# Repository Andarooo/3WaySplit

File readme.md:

# 3 Way Split

### An open source split keyboard. (yeah we really needed more of those (¬_¬) )

## Layout

As you might have guessed this keyboard is split into 3 parts. A left, right and numpad.
Left and right is split in the middle but follows a standard layout with the right side squished in and a couple extra macros for use on the left side.
Numpad has a couple extra macro keys as well if you want to use them.

## Firmware

Keyboard was made with intention to utilise [ZMK](https://zmk.dev/)
I have made a [matching ZMK repo](https://github.com/Andarooo/zmk-3waysplit) with config setup to take the expected layout with the assumption of a nice!nano or equivalent dev board has been used.

## Start Here

Let's say you want to take my slop of gerbers and STLs and make a functional keyboard what are we going to need?
 - Time & money
 - A 3D printer or a 3d printer service
 - A soldering iron
 - Time & money
 - Access to a PCB printing service like PCBWay or JLCPCB
 - A bunch of random crap most likely off Amazon (boo) or Ali-Express (not a boo but it's still not great)
 - Time & money

 If you have enough time and attention span that you're still reading then you might be in a hyperfocus spiral; maybe go get some more coffee. But also keep reading in order and you should have a decent idea on how to get this keeb up and running. I'll try to structure everything in the order that you would expect to do it in. Anyway, without further ado let's throw ourselves into:

 ## Parts

 So here's a list of all the random bits to get off your horrifying conglomerate market of choice:
 - SOD-123 diodes (107)
    - I went for 1n4148 but any that'll fit the sod-123 form and work with keebs will do.
 - Hotswap sockets (107)
    - These PCBs were made with the intended use of kailh hotswap sockets, any that fit will work so don't get too precious about it
 - Developer boards (3). 
    - The PCBs are made with the nice!nano in mind, you could modify the PCB files and regenerate gerbers and change that but if you're cabable of that why are you looking at my crappy design?
    - You could also use any of the knock of nice!nanos which are significantly cheaper (sorry Nick Winans); especially if you live outside the US. (googling pro micro or nice!nano will probably get you somewhere) 
        - The companies that make these are kinda trash because they're exploiting someone else's R&D. I you can buy the real deal pls do, but also business is business y'know.
    - You'll need one per part of the keeb so go ahead and buy 3.
 - M3 screw hot inserts.
    - You use a soldering iron to push these into a slot which adds a threaded insert so you can screw stuff together.
    - These are relatively cheap and you can buy the special soldering iron tips for pushing them in but you don't actually NEED them most of the time.
 - M3 screws.
    - What did you think the inserts were for?
    - You'll likely need a few sizes between 4mm to 20mm so I'd recommend just buying one of those assorted packs.
    - I chose to use allen/hex screws but any will do as long as the heads fit in the hole provided.
 - Keyswitches
    - It is a custom keeb, so I'd assume you knew about this one if you're reading this.
    - There's honestly too many options for me to go into here so I guess just google it or watch some weird cringy keebfluencer.
 - Keycaps
    - See above.
    - I did mess up and chose to have a 2.5u spacebar without realising they're actually pretty uncommon so you can eiter just use a 2.25u with a gap or go track one down. Most sets will have the 3u spacebar that I designed the right side for
 - Key stabilisers
    - These are for the longer keys.
    - All the stab slots are meant for the regular 2u stabs so don't get a spacebar stab; it won't get used. (I think there's 7?)
 - USB C cables to flash firmware and charge etc.

## PCB Printing

So this bit is actually way easier than it sounds, but you jump on the website of the pcb printer of our choice and upload the gerbers which are in the [gerber directory](https://github.com/Andarooo/3WaySplit/tree/main/PCB/Gerbers). It'll take a little while and for the most part just choose the standard settings. We only need the regular 2 layer PCB and also change the mask colour to whatever you'd like to see (I got purple).

## PCB Assembly

This keeb is actually pretty easy to assemble because I couldn't figure out how to get LEDs or even the caps/num/scroll locks lights working.

The keeb has 107 keys in total, does that mean you'll be soldering 107 parts? No of course not, you'll be soldering about 215. The parts that need to be soldered are SMD (Surface Mount Device) which are finicky as fuck to attach to a board if you don't know what the hell you're doing.

If you don't have any soldering experience you'll first want:
 - A soldering iron.
    - I recommend a cheap modern temperature controlled one like a pinecil or ts101 you'll need a fast charging brick that pumps out like 65W and a decent USB C cable too to power it. (Yes different cables will deliver different amounts of power)
 - Solder
    - I'd recommend leaded flux core as it's much easier to melt and work with, just don't lick it I guess.
 - Tip Tinner
    - It's like a powder which keeps your tip tinned (metal and shiny).
 - Flux resin/flux pen
    - For when the solder just doesn't wanna stick.
 - Wet sponge/paper towel
    - Gotta keep that tip clean.
 - A decent video on how to solder.

Soldering SMD parts can be annoying but in general it comes down to 3 steps:
1. Melt some solder onto 1 (not both) pad.
2. Put the part on and re-melt the solder to attach the part.
3. Add solder to the other pad to connect up the other side of the part.

It's much easier to do the sockets than the diodes because I'm an idiot and thought it'd be fun to choose the smaller SMD form factor.

***REMEMBER THAT DIODES HAVE A DIRECTION***

Don't solder them around the wrong way or the switch will not work. There's a thin line on one side which shows the cathode (-). This needs to go away from the the socket so make sure the side that you're soldering to the trace that goes straight to the socket doesn't have the line.

Similarly don't put the sockets on upside down, It'll be really obvious because you'll cover the hole that the middle of the switch usually goes in.

If you mess anything up then watch some videos on desoldering and buy some solder wick or a sucker I guess.

For the microcontroller board, there is some assumptions that I've made with regards to how it's mounted in my case design. If you don't want to mount it the same way I have planned then go and modify the case STLs. It's meant to be mounted with the standoffs on the underside of the case. The bottom of the dev board should be exposed. Just make sure the pins on the dev board match the keeb PCB and you should be sweet. Measure twice cut once. The USB C port should be exposed to the hole in the case if everything has been done right.

## Printing the case

This bit should be pretty straightforward if you've done some 3d printing before. 

There are 3 sets of parts; the plates, the enclosures and the feet. I would recommend printing the plates first to get an idea of how well your printer will handle it and if it will fit the build. The right side is the largest so if you can print the right enclosure you'll be g.

The case STLs are made up of a top and bottom piece, I'll leave that to you to work out on the slicer. They attach together later using the m3 screws and inserts.

I've never used a 3D printing service before so If you want to go that route I wish you luck but I can't provide advice.

## Adding the heated inserts

This part is actually pretty fun and satisfying. So as I alluded to earlier you can buy these special soldering iron tips that fit into the top of the m3 inserts. You don't need it and it doesn't make much difference TBH but It'll probably save you from accidentally poking the back of the hole with the tip of your iron.

There's not a whole lot to this really. make sure the insert is the right way around with the thinner bit going in first then push it in with the tip of your soldering iron giving light even pressure until it's fully seated. Preferably it should be flush with the surface, but if it goes a bit deep you just might need a slightly longer screw so nothing that bad. Try to keep it going in straight if you can.

Each top part of the enclosure has slots where the inserts are meant to go to support screws from the bottom.
Each bottom part has slots for where the feet will attach. ***Do not put the inserts in the screw holes which go all the way through**

## Firmware + Test

You should probably flash the firmware before you assemble as you'll need access to the controller boards to put them into bootloader mode. First go to the [zmk-3waysplit](https://github.com/Andarooo/zmk-3waysplit) repo and navigate to actions (near the top). Then click on the last successful workflow run and scroll down to the Artifacts where there should be a firmware artifact which you can download. After downloading this you should be able to unzip each of the firmwares for each part.

Connect the board to the pc using a USB C cable and it should enter in bootloader mode where it will essentially open as a mounted drive (like a flash drive or similar) if it isn't in bootloader mode simply short the reset pin to the ground (should be next to it) twice in quick succession using some wire or tweezers etc.

Now simply copy the appropriate firmware file onto the root directory of the drive and it should reset. You should now essentially have a working keeb or part there of. And can test each switch by shorting the contacts on each slot again using wire or tweezers or something else metal. I would reccommend testing the whole keeb before assembly as now is the best time to fix dodgy soldering etc.

## Assembly

This is the real fun bit where everything comes together. Assuming you've done everything right this should be a cakewalk.

Make sure to put in your stabilisers before the switches, you can watch a video or just work it out. It's not rocket science

Then start by adding a couple switches into their slots in the plate, preferably on the corners then push the the switches into their PCB slots to marry the PCB and plate together. Make sure you put the switches in the right direction and orientation when attaching to the plate; though it will be pretty obvious if you mess up and can be easily remedied.

Once that's done add the switches one by one making sure they're fully inserted into the pcb and clicked into place in the plate. It's easy to bend a pin if you're not paying attention while adding the switch to the pcb slot. If this happens just carefully remove it and try and bend the pin straight again with some pliers or something then be careful putting it back in this time. Always worth having a few spare switches for this reason.

Once all your switches are all inserted it's time to assemble the enclosures. It all fits together like a sandwich with the plate in between. Do a dry fit first to get an idea of how the keeb will all go together and don't force anything; any printing defects can be cut or sanded to fit so don't break stuff because you thought yourself a caveman.

I would also recommend putting some padding where the plate gets sandwiched into the case to help with noise. I just used some double sided foam tape with the plastic linine unremoved. This is the "gasket" in gasket mounted design. No clue if it actually does anything to the sound so feel free to explore this.

Screws go in from the bottom into the inserts in the top. There are various sizes for each part. The numpad should be 2x 20mm screws and 2x 16mm screws. I designed it first; can you tell? The others should all be 10 or 12 depending how deep you added the inserts.

Now it's time to add your keycaps. If you bought a set they should be in the correct arangement. Otherwise I guess refer to the [layouts](https://github.com/Andarooo/3WaySplit/tree/main/Layout) I've made as to where everything should go. or just google it I guess. You can also change the layout with your own by forking the zmk config I have and making your own. Crazy huh?

The feet attach with a couple of 4mm screws and should face with the rounded side of the feet towards the front of the keeb.

And that's it. Thanks for reading all of this. It took me an evening to write up so I hope someone gets through it.

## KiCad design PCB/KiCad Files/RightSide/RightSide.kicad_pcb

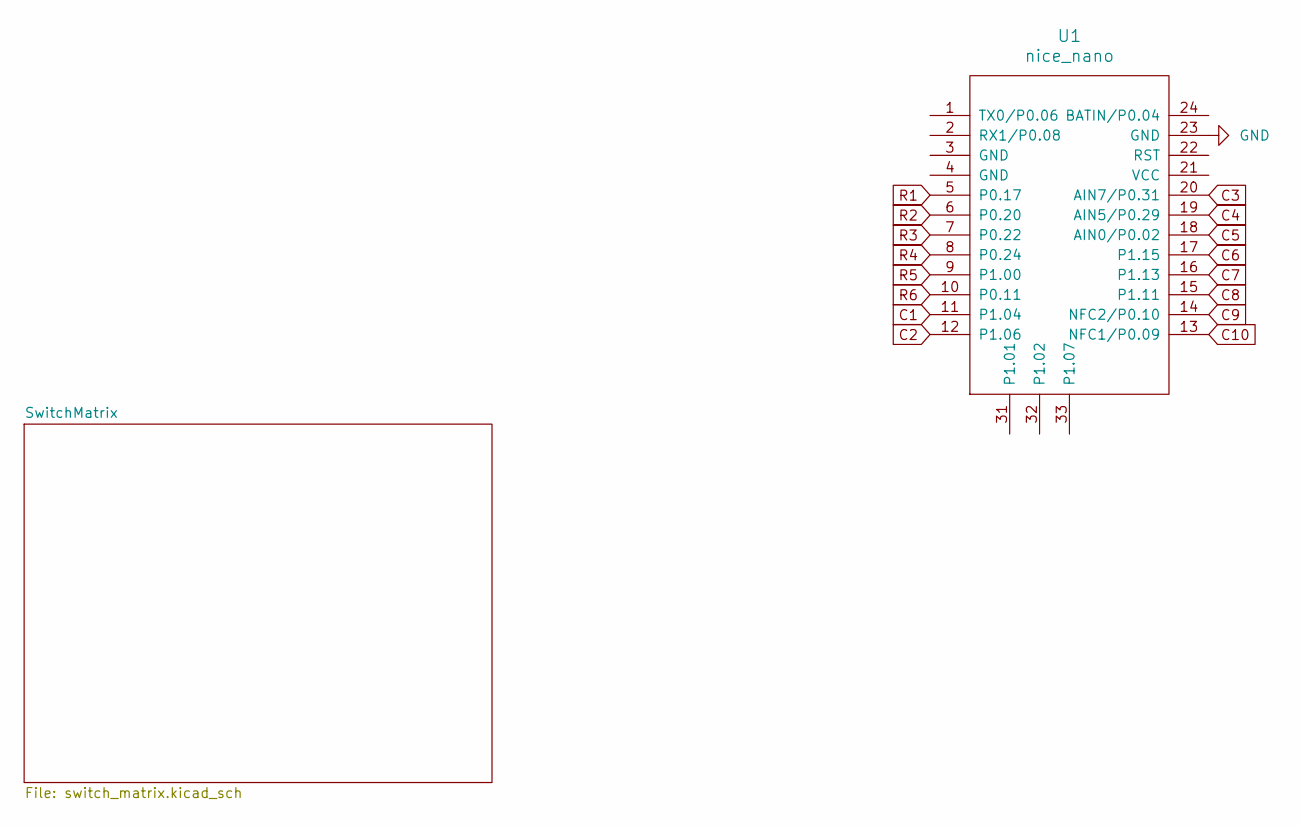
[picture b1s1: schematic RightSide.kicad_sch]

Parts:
U1: nice_nano

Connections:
C1: U1.11 (P1.04); also elsewhere on the board
C2: U1.12 (P1.06); also elsewhere on the board
C3: U1.20 (AIN7/P0.31); also elsewhere on the board
C4: U1.19 (AIN5/P0.29); also elsewhere on the board
C5: U1.18 (AIN0/P0.02); also elsewhere on the board
C6: U1.17 (P1.15); also elsewhere on the board
C7: U1.16 (P1.13); also elsewhere on the board
C8: U1.15 (P1.11); also elsewhere on the board
C9: U1.14 (NFC2/P0.10); also elsewhere on the board
C10: U1.13 (NFC1/P0.09); also elsewhere on the board
GND: U1.23 (GND)
R1: U1.5 (P0.17); also elsewhere on the board
R2: U1.6 (P0.20); also elsewhere on the board
R3: U1.7 (P0.22); also elsewhere on the board
R4: U1.8 (P0.24); also elsewhere on the board
R5: U1.9 (P1.00); also elsewhere on the board
R6: U1.10 (P0.11); also elsewhere on the board

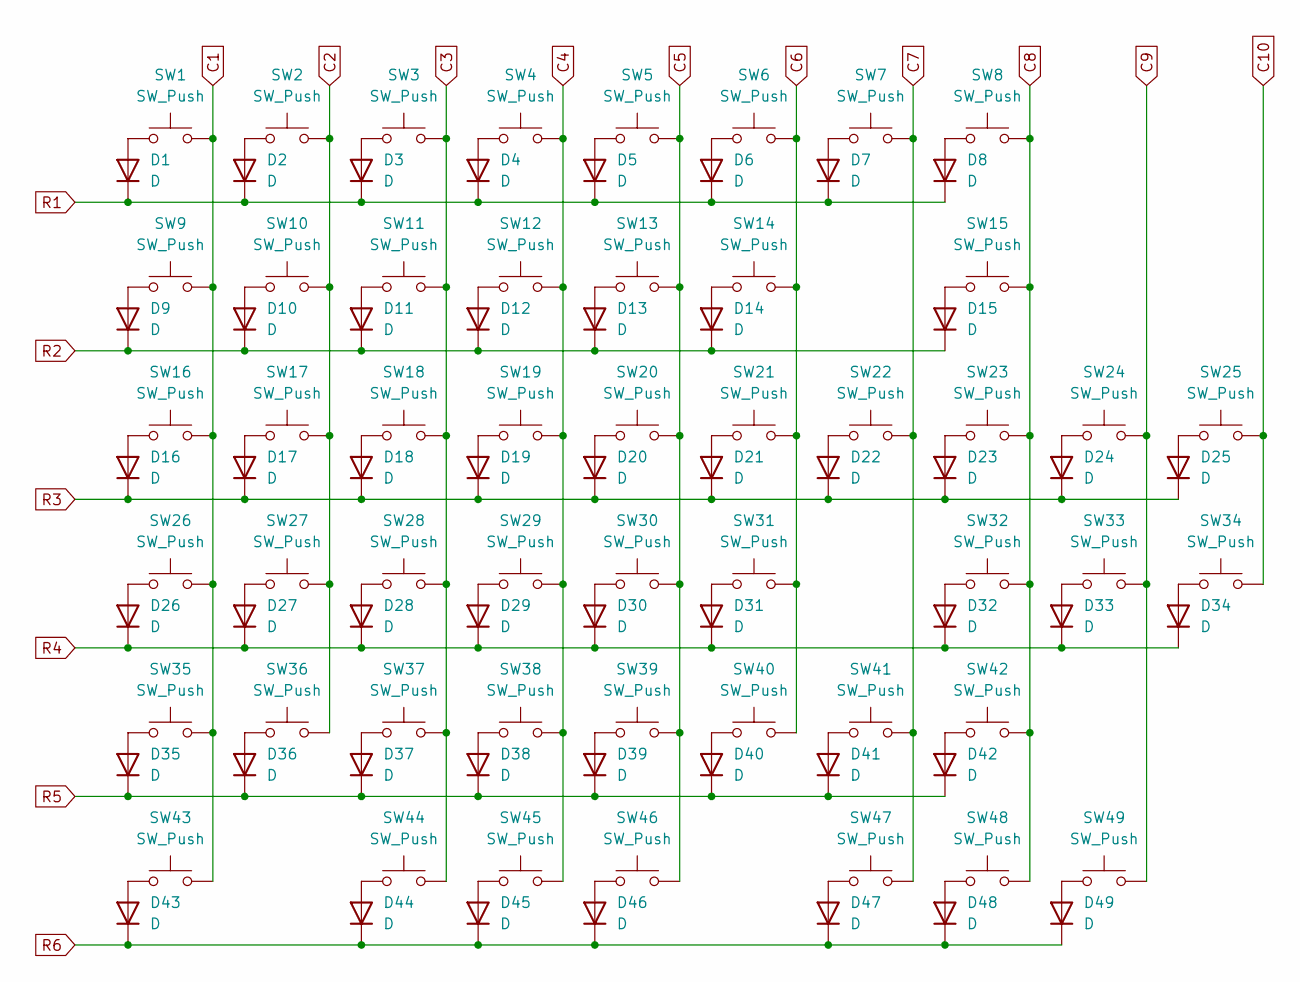
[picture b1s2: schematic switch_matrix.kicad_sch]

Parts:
D1, D2, D3, D4, D5, D6, D7, D8, D9, D10, D11, D12, D13, D14, D15, D16, D17, D18, D19, D20, D21, D22, D23, D24, D25, D26, D27, D28, D29, D30, D31, D32, D33, D34, D35, D36, D37, D38, D39, D40, D41, D42, D43, D44, D45, D46, D47, D48, D49: D; D_SOD-123
SW1, SW2, SW3, SW4, SW5, SW6, SW7, SW8, SW9, SW10, SW11, SW12, SW13, SW14, SW16, SW17, SW18, SW19, SW20, SW21, SW22, SW24, SW25, SW26, SW27, SW28, SW29, SW30, SW31, SW33, SW34, SW35, SW36, SW37, SW38, SW39, SW40, SW42, SW47, SW48, SW49: SW_Push; SW_Hotswap_Kailh_MX_1.00u
SW15: SW_Push; SW_Hotswap_Kailh_MX_2.00u
SW23: SW_Push; SW_Hotswap_Kailh_MX_1.50u
SW32: SW_Push; SW_Hotswap_Kailh_MX_2.25u
SW41: SW_Push; SW_Hotswap_Kailh_MX_1.75u
SW43: SW_Push; SW_Hotswap_Kailh_MX_3.00u
SW44, SW45, SW46: SW_Push; SW_Hotswap_Kailh_MX_1.25u

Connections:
C1: SW1.2, SW9.2, SW16.2, SW26.2, SW35.2, SW43.2; also elsewhere on the board
C2: SW2.2, SW10.2, SW17.2, SW27.2, SW36.2; also elsewhere on the board
C3: SW3.2, SW11.2, SW18.2, SW28.2, SW37.2, SW44.2; also elsewhere on the board
C4: SW4.2, SW12.2, SW19.2, SW29.2, SW38.2, SW45.2; also elsewhere on the board
C5: SW5.2, SW13.2, SW20.2, SW30.2, SW39.2, SW46.2; also elsewhere on the board
C6: SW6.2, SW14.2, SW21.2, SW31.2, SW40.2; also elsewhere on the board
C7: SW7.2, SW22.2, SW41.2, SW47.2; also elsewhere on the board
C8: SW8.2, SW15.2, SW23.2, SW32.2, SW42.2, SW48.2; also elsewhere on the board
C9: SW24.2, SW33.2, SW49.2; also elsewhere on the board
C10: SW25.2, SW34.2; also elsewhere on the board
unnamed: D1.2 (A), SW1.1
unnamed: D2.2 (A), SW2.1
unnamed: D3.2 (A), SW3.1
unnamed: D4.2 (A), SW4.1
unnamed: D5.2 (A), SW5.1
unnamed: D6.2 (A), SW6.1
unnamed: D7.2 (A), SW7.1
unnamed: D8.2 (A), SW8.1
unnamed: D9.2 (A), SW9.1
unnamed: D10.2 (A), SW10.1
unnamed: D11.2 (A), SW11.1
unnamed: D12.2 (A), SW12.1
unnamed: D13.2 (A), SW13.1
unnamed: D14.2 (A), SW14.1
unnamed: D15.2 (A), SW15.1
unnamed: D16.2 (A), SW16.1
unnamed: D17.2 (A), SW17.1
unnamed: D18.2 (A), SW18.1
unnamed: D19.2 (A), SW19.1
unnamed: D20.2 (A), SW20.1
unnamed: D21.2 (A), SW21.1
unnamed: D22.2 (A), SW22.1
unnamed: D23.2 (A), SW23.1
unnamed: D24.2 (A), SW24.1
unnamed: D25.2 (A), SW25.1
unnamed: D26.2 (A), SW26.1
unnamed: D27.2 (A), SW27.1
unnamed: D28.2 (A), SW28.1
unnamed: D29.2 (A), SW29.1
unnamed: D30.2 (A), SW30.1
unnamed: D31.2 (A), SW31.1
unnamed: D32.2 (A), SW32.1
unnamed: D33.2 (A), SW33.1
unnamed: D34.2 (A), SW34.1
unnamed: D35.2 (A), SW35.1
unnamed: D36.2 (A), SW36.1
unnamed: D37.2 (A), SW37.1
unnamed: D38.2 (A), SW38.1
unnamed: D39.2 (A), SW39.1
unnamed: D40.2 (A), SW40.1
unnamed: D41.2 (A), SW41.1
unnamed: D42.2 (A), SW42.1
unnamed: D43.2 (A), SW43.1
unnamed: D44.2 (A), SW44.1
unnamed: D45.2 (A), SW45.1
unnamed: D46.2 (A), SW46.1
unnamed: D47.2 (A), SW47.1
unnamed: D48.2 (A), SW48.1
unnamed: D49.2 (A), SW49.1
R1: D1.1 (K), D2.1 (K), D3.1 (K), D4.1 (K), D5.1 (K), D6.1 (K), D7.1 (K), D8.1 (K); also elsewhere on the board
R2: D9.1 (K), D10.1 (K), D11.1 (K), D12.1 (K), D13.1 (K), D14.1 (K), D15.1 (K); also elsewhere on the board
R3: D16.1 (K), D17.1 (K), D18.1 (K), D19.1 (K), D20.1 (K), D21.1 (K), D22.1 (K), D23.1 (K), D24.1 (K), D25.1 (K); also elsewhere on the board
R4: D26.1 (K), D27.1 (K), D28.1 (K), D29.1 (K), D30.1 (K), D31.1 (K), D32.1 (K), D33.1 (K), D34.1 (K); also elsewhere on the board
R5: D35.1 (K), D36.1 (K), D37.1 (K), D38.1 (K), D39.1 (K), D40.1 (K), D41.1 (K), D42.1 (K); also elsewhere on the board
R6: D43.1 (K), D44.1 (K), D45.1 (K), D46.1 (K), D47.1 (K), D48.1 (K), D49.1 (K); also elsewhere on the board

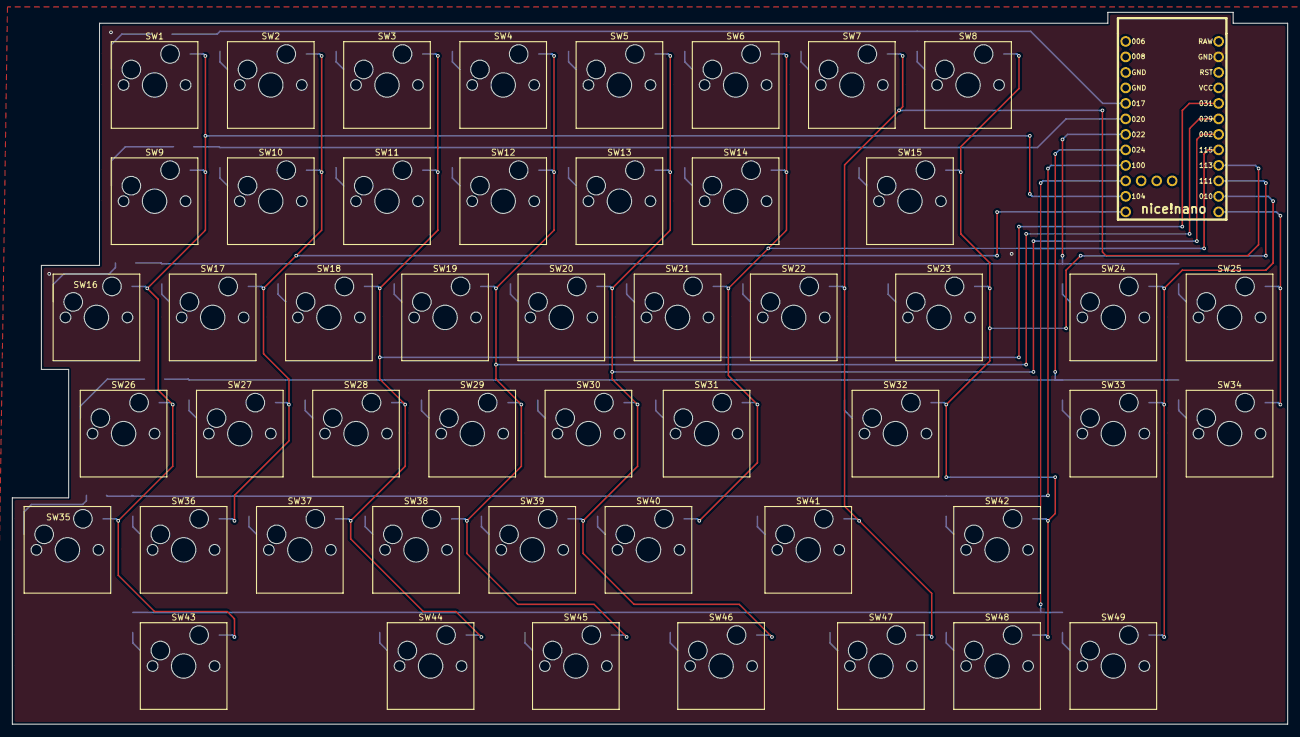
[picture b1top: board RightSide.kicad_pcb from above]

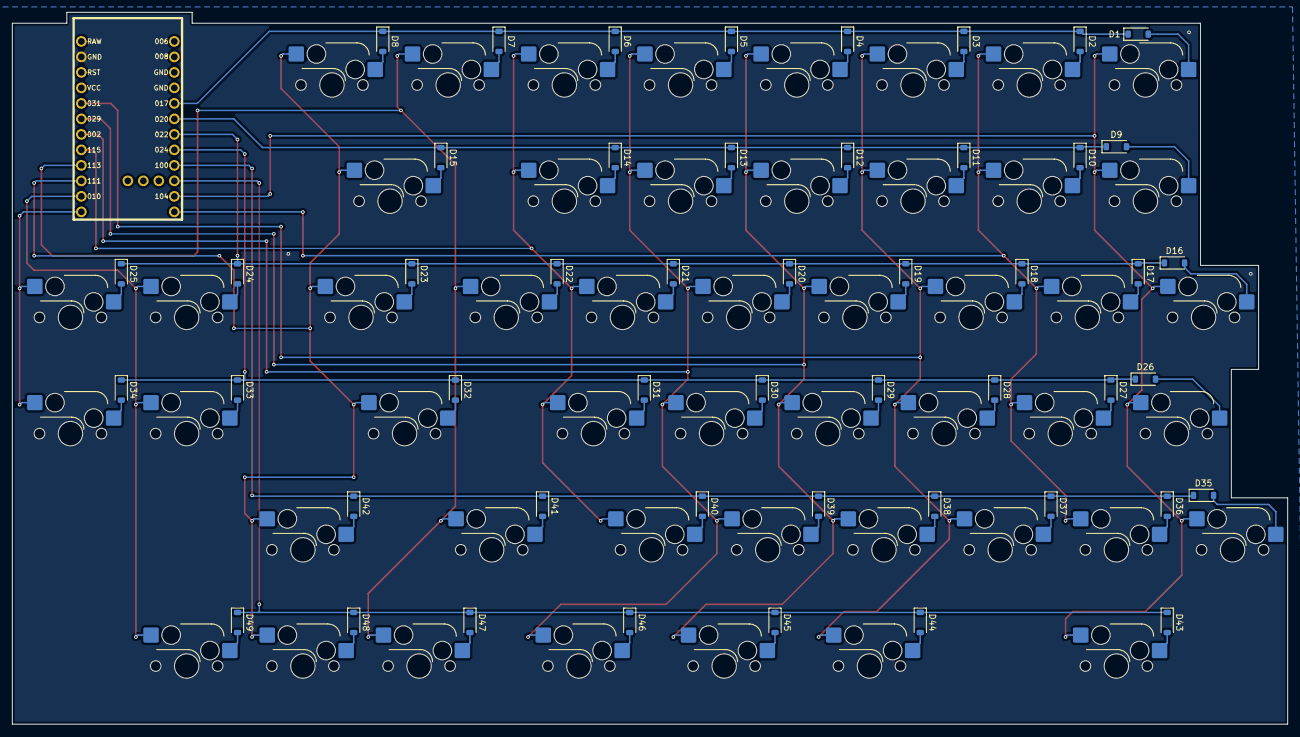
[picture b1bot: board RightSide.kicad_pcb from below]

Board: 2 copper layers, 209.0 x 116.7 mm, 99 parts (49 on the bottom side), 65 nets.
